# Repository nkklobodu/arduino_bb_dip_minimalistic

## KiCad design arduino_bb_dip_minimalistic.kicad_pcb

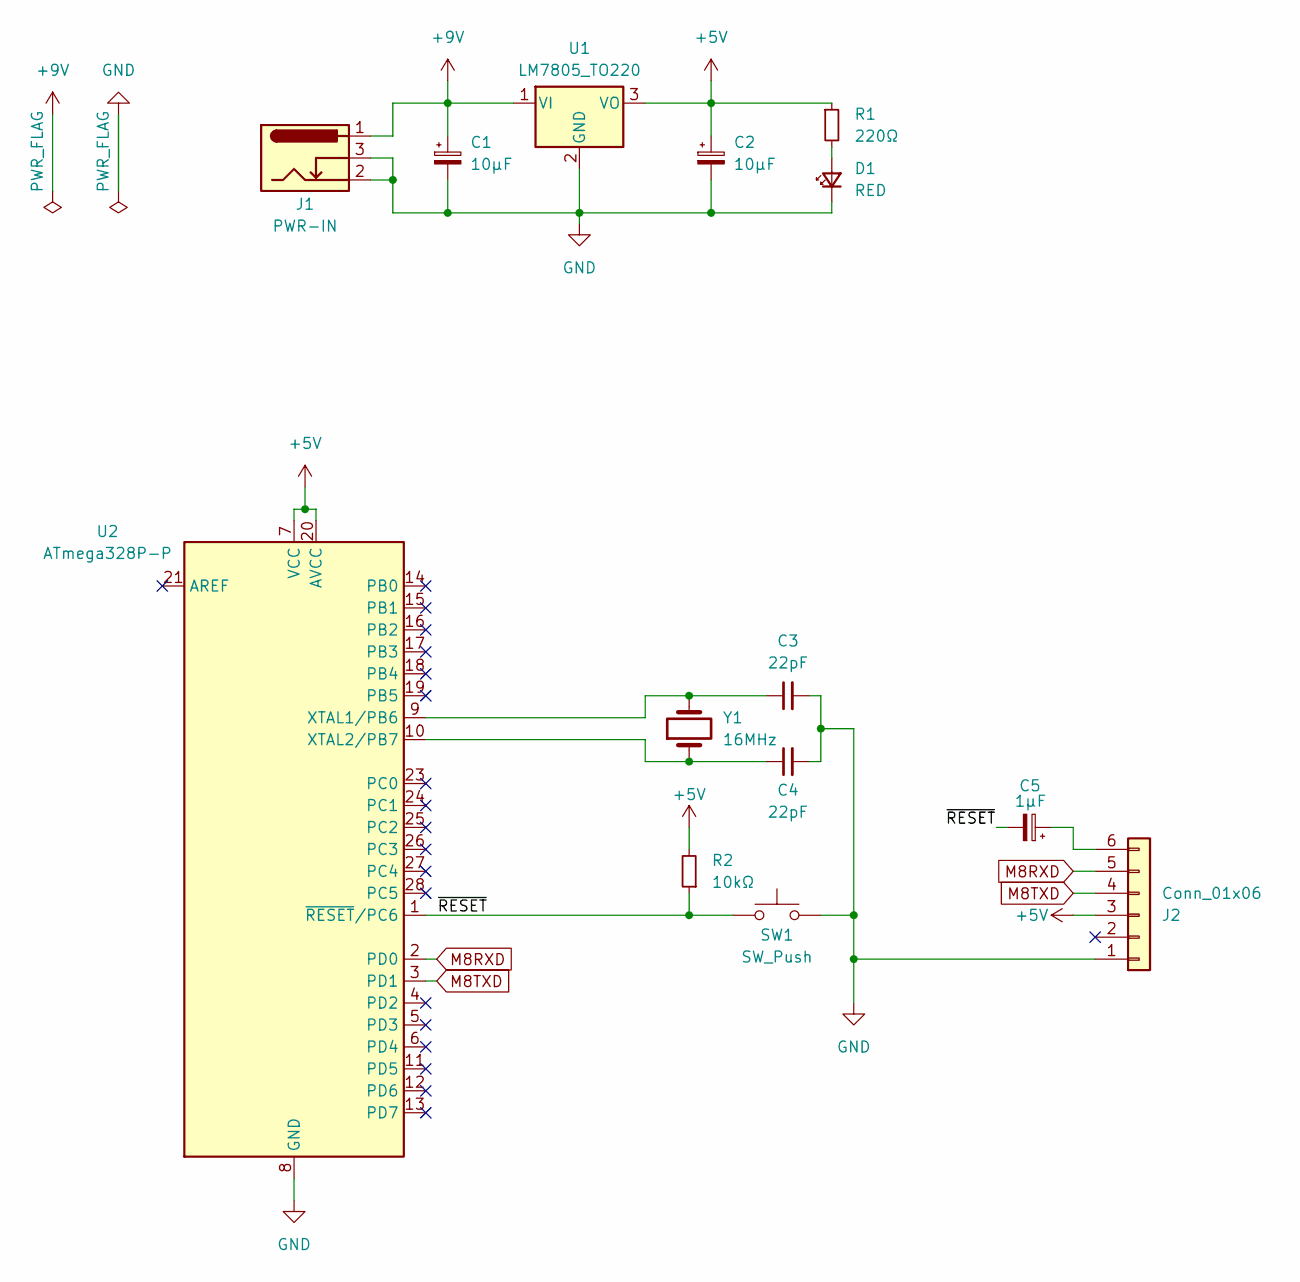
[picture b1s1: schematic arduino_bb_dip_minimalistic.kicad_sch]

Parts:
C1, C2: 10µF; CP_Radial_D8.0mm_P2.50mm
C3, C4: 22pF; C_Disc_D6.0mm_W4.4mm_P5.00mm
C5: 1µF; CP_Radial_D5.0mm_P2.50mm
D1: RED; LED_D3.0mm
J1: PWR-IN; BarrelJack_Horizontal
J2: Conn_01x06; PinSocket_1x06_P2.00mm_Vertical
R1: 220Ω; R_Axial_DIN0207_L6.3mm_D2.5mm_P10.16mm_Horizontal
R2: 10kΩ; R_Axial_DIN0207_L6.3mm_D2.5mm_P10.16mm_Horizontal
SW1: SW_Push; SW_PUSH_6mm_H5mm
U1: LM7805_TO220; TO-220-3_Vertical
U2: ATmega328P-P; DIP-28_W7.62mm
Y1: 16MHz; Crystal_HC49-4H_Vertical

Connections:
+5V: C2.1, J2.3, R1.1, R2.2, U1.3 (VO), U2.7 (VCC), U2.20 (AVCC)
+9V: C1.1, J1.1, U1.1 (VI)
/~RESET: C5.2, R2.1, SW1.1, U2.1 (~RESET/PC6)
GND: C1.2, C2.2, C3.2, C4.2, D1.1 (K), J1.2, J1.3, J2.1, SW1.2, U1.2 (GND), U2.8 (GND), U2.22 (GND)
M8RXD: J2.5, U2.2 (PD0)
M8TXD: J2.4, U2.3 (PD1)
unnamed: D1.2 (A), R1.2
unnamed: C5.1, J2.6
unnamed: C3.1, U2.9 (XTAL1/PB6), Y1.2
unnamed: C4.1, U2.10 (XTAL2/PB7), Y1.1

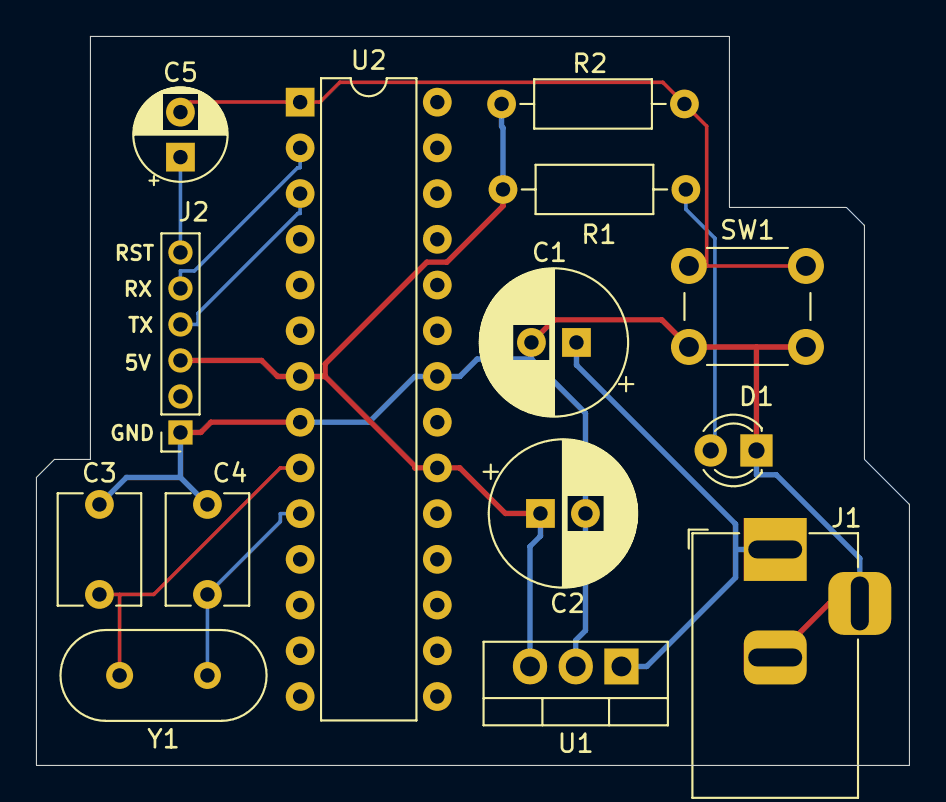
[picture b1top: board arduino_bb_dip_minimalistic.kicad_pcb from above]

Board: 2 copper layers, 48.5 x 40.5 mm, 14 parts (0 on the bottom side), 10 nets.
